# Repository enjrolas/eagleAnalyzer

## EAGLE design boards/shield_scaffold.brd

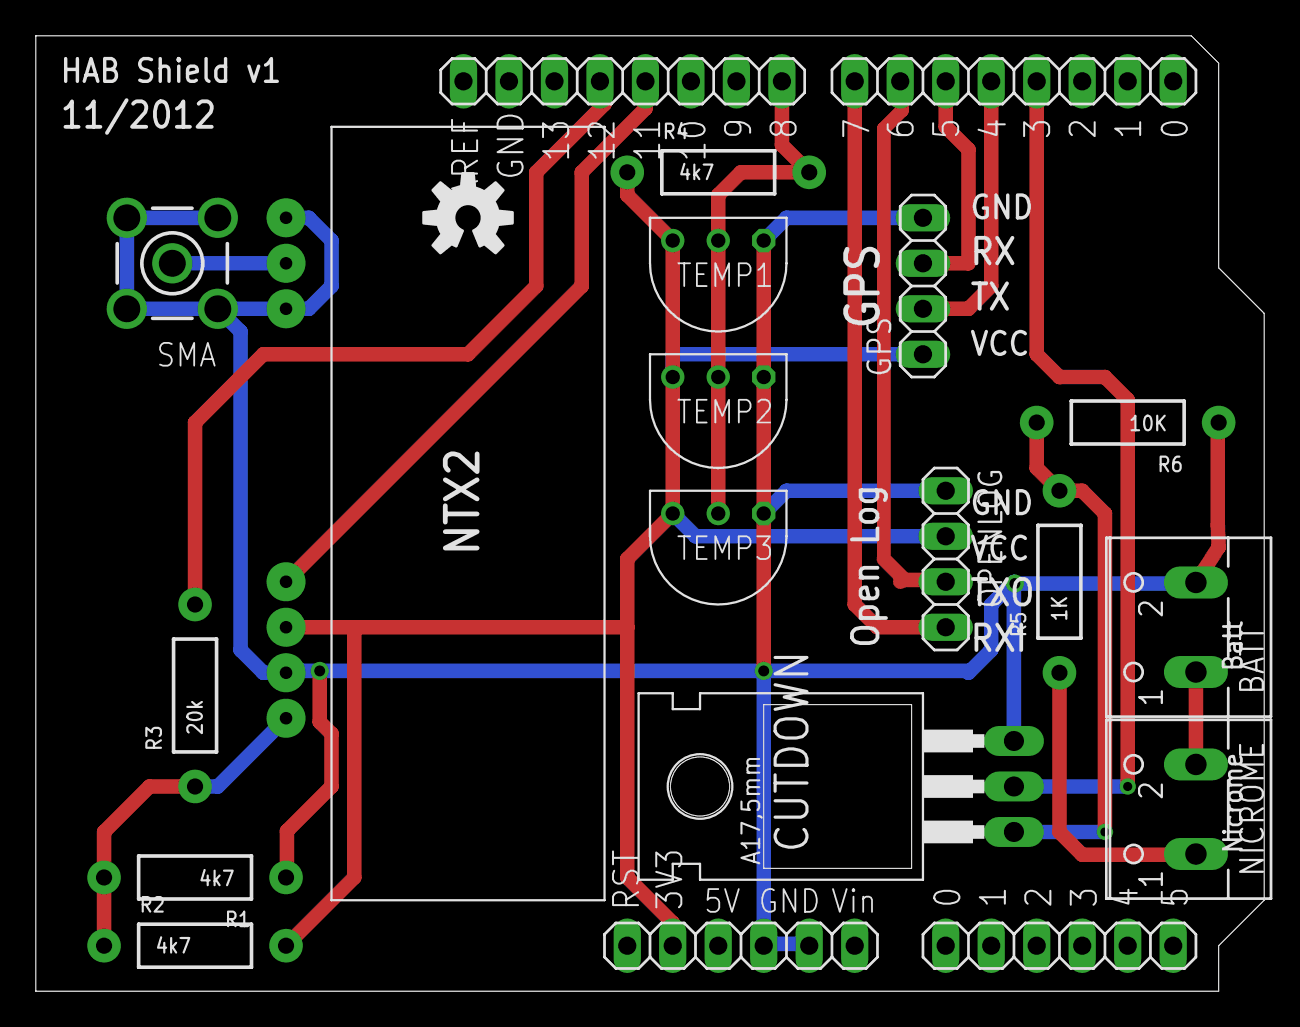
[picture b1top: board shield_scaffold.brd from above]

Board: 2 copper layers, 68.6 x 53.3 mm, 21 parts (0 on the bottom side), 16 nets.

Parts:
BATT: 9V; W237-102
CUTDOWN: BUZ21; TO220
GPS: 1X04
NICROME: Wire; W237-102
OPENLOG: 1X04
R1, R2, R4: 4k7; AXIAL-0.4
R3: 20k; AXIAL-0.4
R5: 1K; AXIAL-0.4
R6: 10K; AXIAL-0.4
SMA: LTI-SASF54GT
TEMP1, TEMP2, TEMP3: DS1821
U$1: POWER; 1X06
U$2: ANALOG; 1X06
U$3: DIGITAL_0_7; 1X08
U$4: DIGITAL_8_13; 1X08
U$5: NTX2
U$6: OSHW-LOGOM; OSHW-LOGO-M

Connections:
9V+: BATT.1, NICROME.2
CUT: CUTDOWN.2, U$3.5
CUTLOAD: NICROME.1, R5.P$1
GND: BATT.2, CUTDOWN.3, GPS.4, OPENLOG.1, R1.P$1, R6.P$1, SMA.3, SMA.4, SMA.5, TEMP1.P$1, TEMP2.P$1, TEMP3.P$1, U$1.4, U$1.5, U$5.0V
GPSRX: GPS.3, U$3.3
GPSTX: GPS.2, U$3.4
LOGI: OPENLOG.4, U$3.1
LOGO: OPENLOG.3, U$3.2
unnamed: CUTDOWN.1, R5.P$2, R6.P$2
NTX2E: U$4.5, U$5.EN
NTX2IO: R3.P$2, U$4.4
RFGND: SMA.2, U$5.RFGND, U$5.RFGND2
RFOUT: SMA.1, U$5.RFOUT
TEMP: R4.P$2, TEMP1.P$2, TEMP2.P$2, TEMP3.P$2, U$4.8
TXD: R1.P$2, R2.P$1, R3.P$1, U$5.TXD
VCC: GPS.1, OPENLOG.2, R2.P$2, R4.P$1, TEMP1.P$3, TEMP2.P$3, TEMP3.P$3, U$1.2, U$5.VCC

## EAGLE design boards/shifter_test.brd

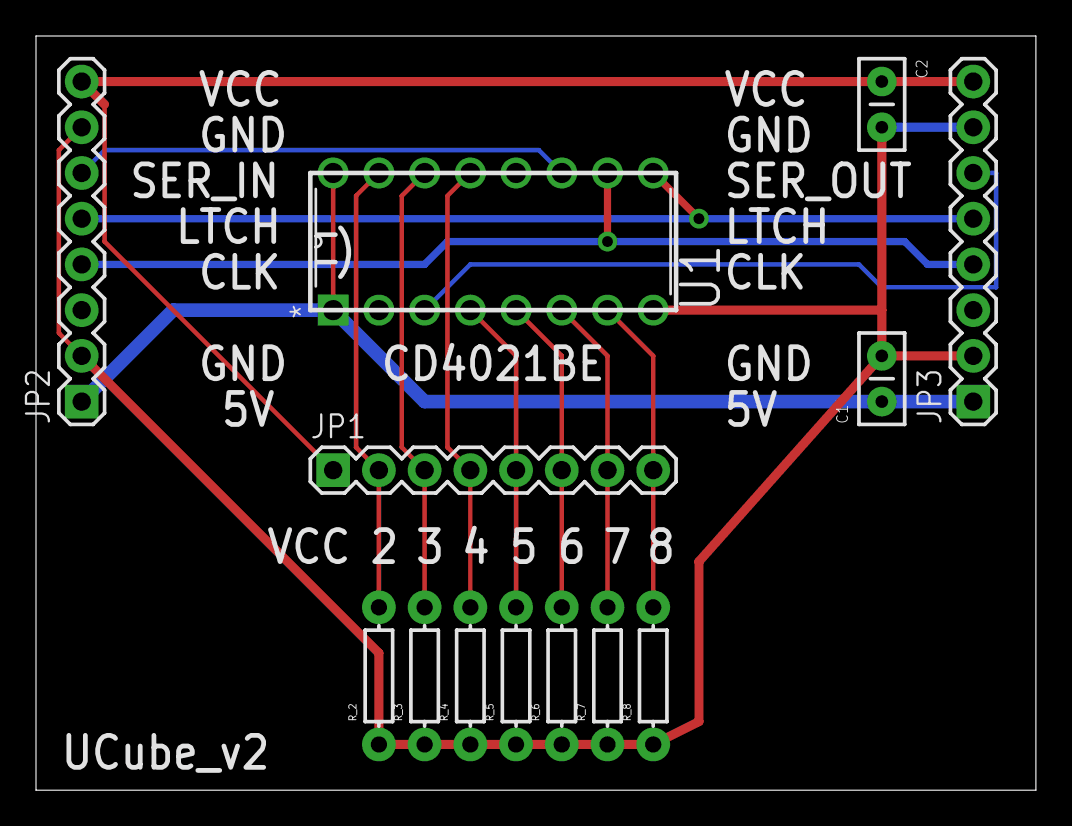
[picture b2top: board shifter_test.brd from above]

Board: 2 copper layers, 55.5 x 41.9 mm, 13 parts (0 on the bottom side), 14 nets.

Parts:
C1, C2: 0.1µf; CAP-PTH-SMALL2
JP1: JP1_LED_HEADER; 1X08
JP2: JP2_SER_IN; 1X08
JP3: JP3_SER_OUT; 1X08
R_2, R_3, R_4, R_5, R_6, R_7, R_8: AXIAL-0.3
U1: CD4021BE; DIP254P762X508-16

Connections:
5V: C1.1, JP2.1, JP3.1, U1.1, U1.16
CLOCK: JP2.4, JP3.4, U1.10
GND: C1.2, C2.2, JP2.2, JP2.7, JP3.2, JP3.7, R_2.P$1, R_3.P$1, R_4.P$1, R_5.P$1, R_6.P$1, R_7.P$1, R_8.P$1, U1.8
LATCH: JP2.5, JP3.5, U1.9
P2: JP1.2, R_2.P$2, U1.15
P3: JP1.3, R_3.P$2, U1.14
P4: JP1.4, R_4.P$2, U1.13
P5: JP1.5, R_5.P$2, U1.4
P6: JP1.6, R_6.P$2, U1.5
P7: JP1.7, R_7.P$2, U1.6
P8: JP1.8, R_8.P$2, U1.7
SERIAL_IN: JP2.6, U1.11
SERIAL_OUT: JP3.6, U1.3
VCC: C2.1, JP1.1, JP2.8, JP3.8

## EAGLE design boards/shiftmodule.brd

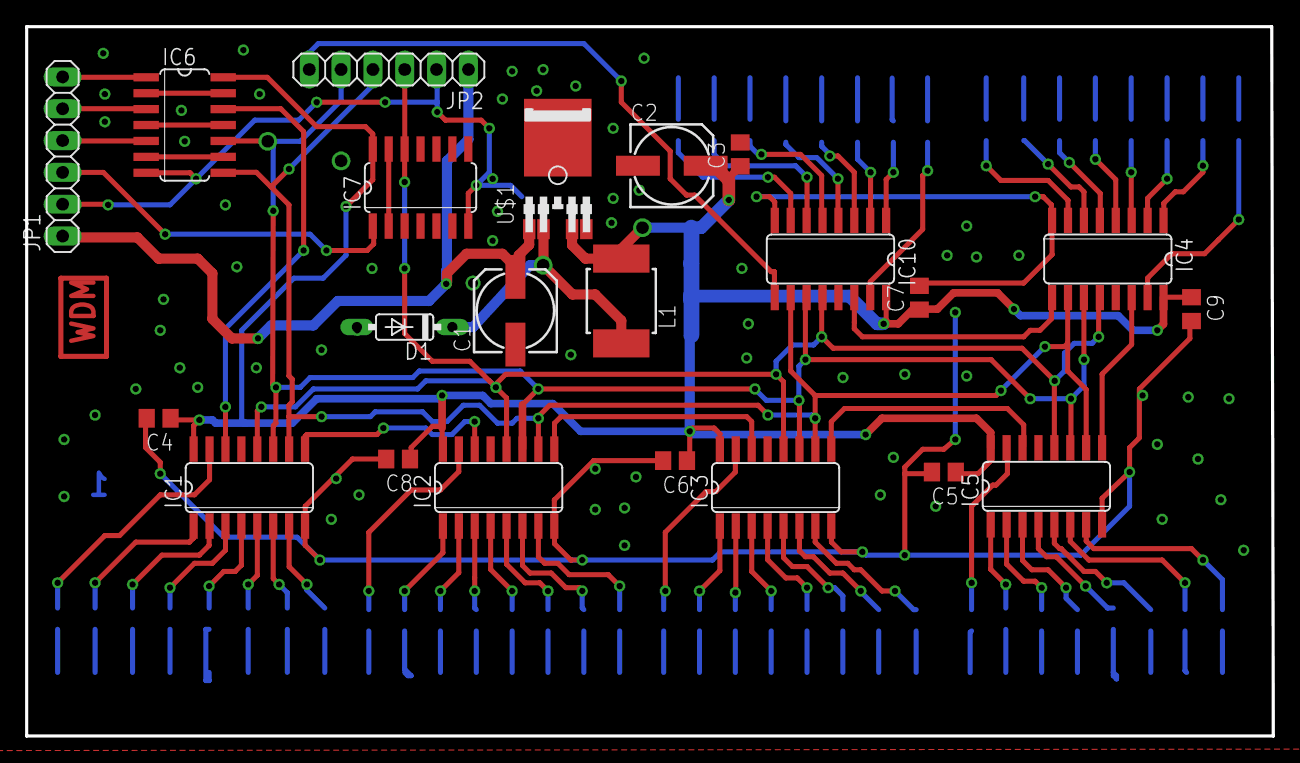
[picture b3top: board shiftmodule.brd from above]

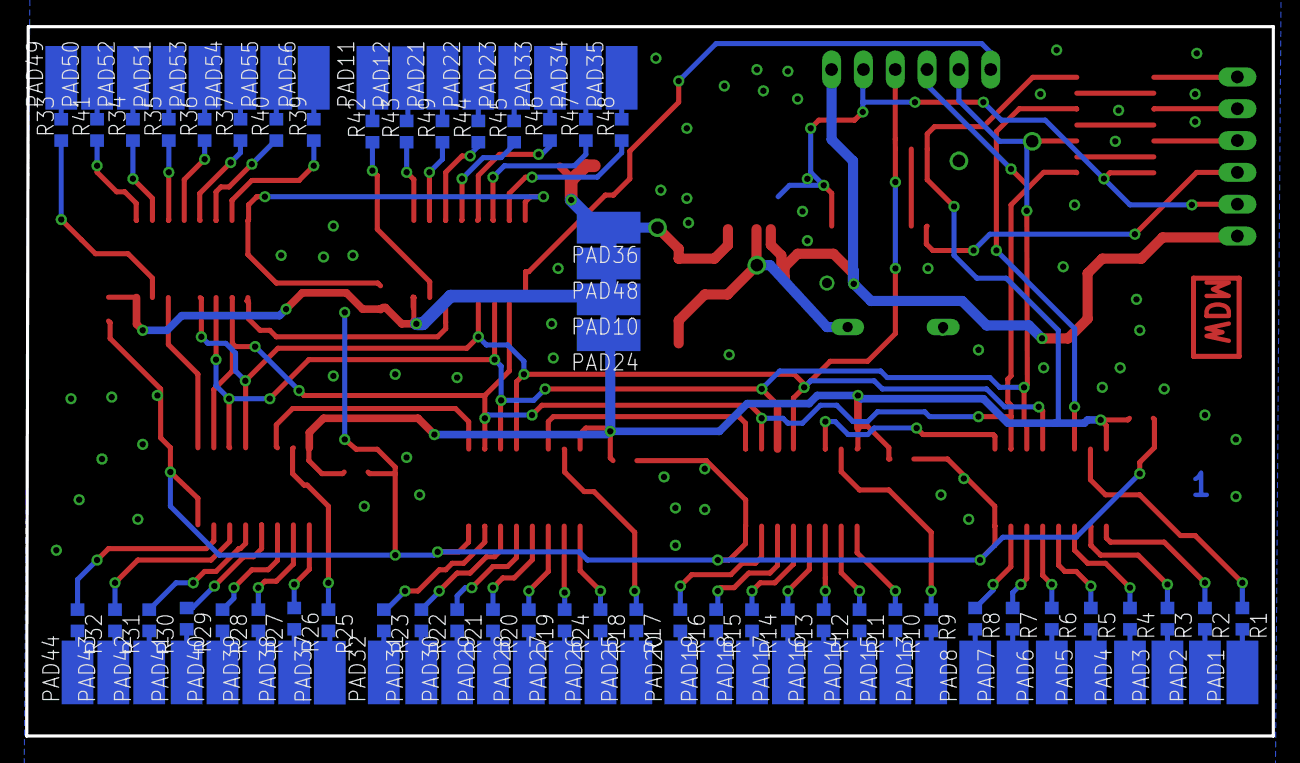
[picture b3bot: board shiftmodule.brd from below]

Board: 2 copper layers, 99.5 x 56.6 mm, 122 parts (100 on the bottom side), 118 nets.

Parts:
C1, C2: 153CLV-0605
C3, C4, C5, C6, C7, C8, C9: C0805
D1: 1N4148DO35-7; DO35-7
IC1, IC2, IC3, IC4, IC5, IC10: 74LS595D; SO16
IC6, IC7: 74HC04D; SO14
JP1, JP2: 1X06
L1: MS85
PAD1, PAD2, PAD3, PAD4, PAD5, PAD6, PAD7, PAD8, PAD10, PAD11, PAD12, PAD13, PAD14, PAD15, PAD16, PAD17, PAD18, PAD19, PAD20, PAD21, PAD22, PAD23, PAD24, PAD25, PAD26, PAD27, PAD28, PAD29, PAD30, PAD31, PAD32, PAD33, PAD34, PAD35, PAD36, PAD37, PAD38, PAD39, PAD40, PAD41, PAD42, PAD43, PAD44, PAD48, PAD49, PAD50, PAD51, PAD52, PAD53, PAD54, PAD55, PAD56: SMD2,54-5,08
R1, R2, R3, R4, R5, R6, R7, R8, R9, R10, R11, R12, R13, R14, R15, R16, R17, R18, R19, R20, R21, R22, R23, R24, R25, R26, R27, R28, R29, R30, R31, R32, R33, R34, R35, R36, R37, R39, R40, R41, R42, R43, R44, R45, R46, R47, R48, R49: R0603
U$1: AP1507; TO252-5-11

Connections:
GND: C1.-, C2.-, C3.2, C4.2, C5.2, C6.2, C7.2, C8.2, C9.2, D1.A, IC1.8, IC2.8, IC3.8, IC4.8, IC5.8, IC6.7, IC7.7, IC10.8, JP1.2, JP2.2, U$1.3, U$1.5
unnamed: IC6.2, IC6.13
unnamed: IC2.9, IC3.14
unnamed: IC3.9, IC5.14
unnamed: IC10.9, JP2.6
unnamed: IC6.4, IC6.11
unnamed: IC6.6, IC6.9
unnamed: IC6.1, JP1.6
unnamed: IC6.3, JP1.5
unnamed: IC6.5, JP1.4
unnamed: IC7.1, JP1.3
unnamed: PAD1.1, R1.2
unnamed: PAD2.1, R2.2
unnamed: PAD3.1, R3.2
unnamed: IC4.14, IC5.9
unnamed: PAD4.1, R4.2
unnamed: PAD5.1, R5.2
unnamed: PAD6.1, R6.2
unnamed: PAD7.1, R7.2
unnamed: PAD8.1, R8.2
unnamed: PAD13.1, R9.2
unnamed: PAD15.1, R10.2
unnamed: PAD14.1, R11.2
unnamed: PAD16.1, R12.2
unnamed: PAD17.1, R13.2
unnamed: PAD18.1, R14.2
unnamed: PAD19.1, R15.2
unnamed: PAD20.1, R16.2
unnamed: PAD25.1, R17.2
unnamed: PAD26.1, R18.2
unnamed: PAD28.1, R19.2
unnamed: PAD29.1, R20.2
unnamed: PAD30.1, R21.2
unnamed: PAD31.1, R22.2
unnamed: PAD32.1, R23.2
unnamed: PAD27.1, R24.2
unnamed: PAD37.1, R25.2
unnamed: PAD38.1, R26.2
unnamed: PAD39.1, R27.2
unnamed: PAD40.1, R28.2
unnamed: PAD41.1, R29.2
unnamed: PAD42.1, R30.2
unnamed: PAD43.1, R31.2
unnamed: PAD44.1, R32.2
unnamed: PAD49.1, R33.2
unnamed: PAD52.1, R34.2
unnamed: PAD51.1, R35.2
unnamed: PAD53.1, R36.2
unnamed: PAD54.1, R37.2
unnamed: PAD56.1, R39.2
unnamed: PAD55.1, R40.2
unnamed: PAD50.1, R41.2
unnamed: IC1.9, IC2.14
unnamed: IC7.2, IC7.13
unnamed: IC4.9, IC10.14
unnamed: PAD11.1, R42.2
unnamed: PAD12.1, R43.2
unnamed: PAD22.1, R44.2
unnamed: PAD23.1, R45.2
unnamed: PAD33.1, R46.2
unnamed: PAD34.1, R47.2
unnamed: PAD35.1, R48.2
unnamed: PAD21.1, R49.2
unnamed: D1.C, L1.1, U$1.2
unnamed: IC4.7, R39.1
unnamed: IC4.5, R37.1
unnamed: IC4.6, R40.1
unnamed: IC4.4, R36.1
unnamed: IC4.3, R35.1
unnamed: IC4.2, R34.1
unnamed: IC4.1, R41.1
unnamed: IC4.15, R33.1
unnamed: IC10.15, R42.1
unnamed: IC10.1, R43.1
unnamed: IC10.2, R49.1
unnamed: IC10.3, R44.1
unnamed: IC10.4, R45.1
unnamed: IC10.5, R46.1
unnamed: IC10.6, R47.1
unnamed: IC10.7, R48.1
unnamed: IC5.7, R32.1
unnamed: IC5.6, R31.1
unnamed: IC5.5, R30.1
unnamed: IC5.4, R29.1
unnamed: IC5.3, R28.1
unnamed: IC5.2, R27.1
unnamed: IC5.1, R26.1
unnamed: IC5.15, R25.1
unnamed: IC3.7, R23.1
unnamed: IC3.6, R22.1
unnamed: IC3.5, R21.1
unnamed: IC3.4, R20.1
unnamed: IC3.3, R19.1
unnamed: IC3.2, R24.1
unnamed: IC3.1, R18.1
unnamed: IC3.15, R17.1
unnamed: IC2.7, R16.1
unnamed: IC2.6, R15.1
unnamed: IC2.5, R14.1
unnamed: IC2.4, R13.1
unnamed: IC2.3, R12.1
unnamed: IC2.2, R11.1
unnamed: IC2.1, R10.1
unnamed: IC2.15, R9.1
unnamed: IC1.15, R1.1
unnamed: IC1.1, R2.1
unnamed: IC1.7, R8.1
unnamed: IC1.6, R7.1
unnamed: IC1.5, R6.1
unnamed: IC1.4, R5.1
unnamed: IC1.3, R4.1
unnamed: IC1.2, R3.1
RCK: IC1.12, IC2.12, IC3.12, IC4.12, IC5.12, IC7.12, IC10.12, JP2.3
SCK: IC1.11, IC2.11, IC3.11, IC4.11, IC5.11, IC6.10, IC10.11, JP2.5
SCL: IC1.10, IC2.10, IC3.10, IC4.10, IC5.10, IC6.8, IC10.10, JP2.4
SER: IC1.14, IC6.12
VCC: C2.+, C3.1, C4.1, C5.1, C6.1, C7.1, C8.1, C9.1, IC1.16, IC2.16, IC3.16, IC4.16, IC5.16, IC6.14, IC7.14, IC10.16, L1.2, PAD10.1, PAD24.1, PAD36.1, PAD48.1, U$1.4
VIN: C1.+, JP1.1, JP2.1, U$1.1

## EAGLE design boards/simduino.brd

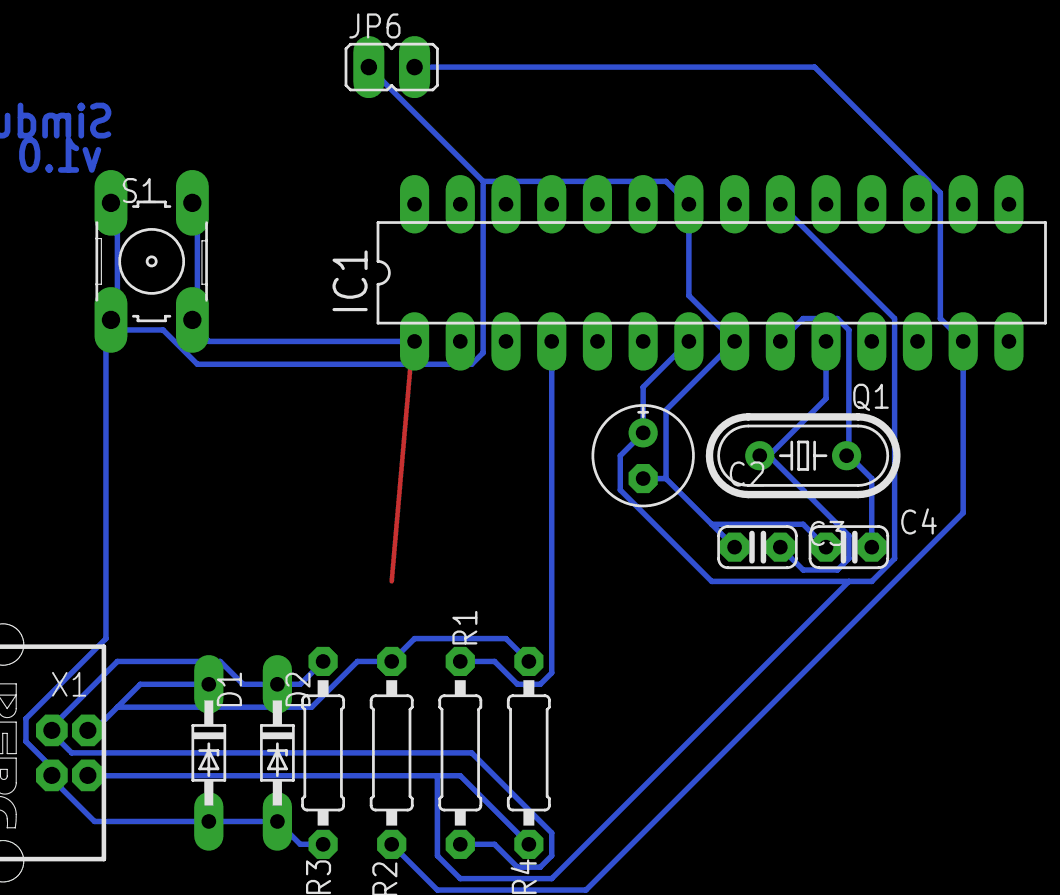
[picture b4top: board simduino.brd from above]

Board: 2 copper layers, 14 parts (0 on the bottom side), 9 nets.

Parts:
C2: 10uF; E2,5-6E
C3, C4: 22p; C025-024X044
D1, D2: 3V6; DO34Z7
IC1: ATMEGA168-20P; DIL28-3
JP6: JP1
Q1: 16MHz; HC49/S
R1, R2: 68; 0207/10
R3: 1M; 0207/10
R4: 1k5; 0207/10
S1: B3F-10XX
X1: PN61729

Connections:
+5USB: C2.+, IC1.7, IC1.20, R4.1, X1.1
D+: D2.C, R1.1, R3.2, X1.3
D-: D1.C, R2.1, R4.2, X1.2
GND: C2.-, C3.1, C4.1, D1.A, D2.A, IC1.8, IC1.22, JP6.1, R3.1, S1.1, S1.2, X1.4
unnamed: IC1.13, JP6.2, R2.2
unnamed: IC1.1, S1.3, S1.4
unnamed: IC1.4, R1.2
unnamed: C3.2, IC1.10, Q1.1
unnamed: C4.2, IC1.9, Q1.2

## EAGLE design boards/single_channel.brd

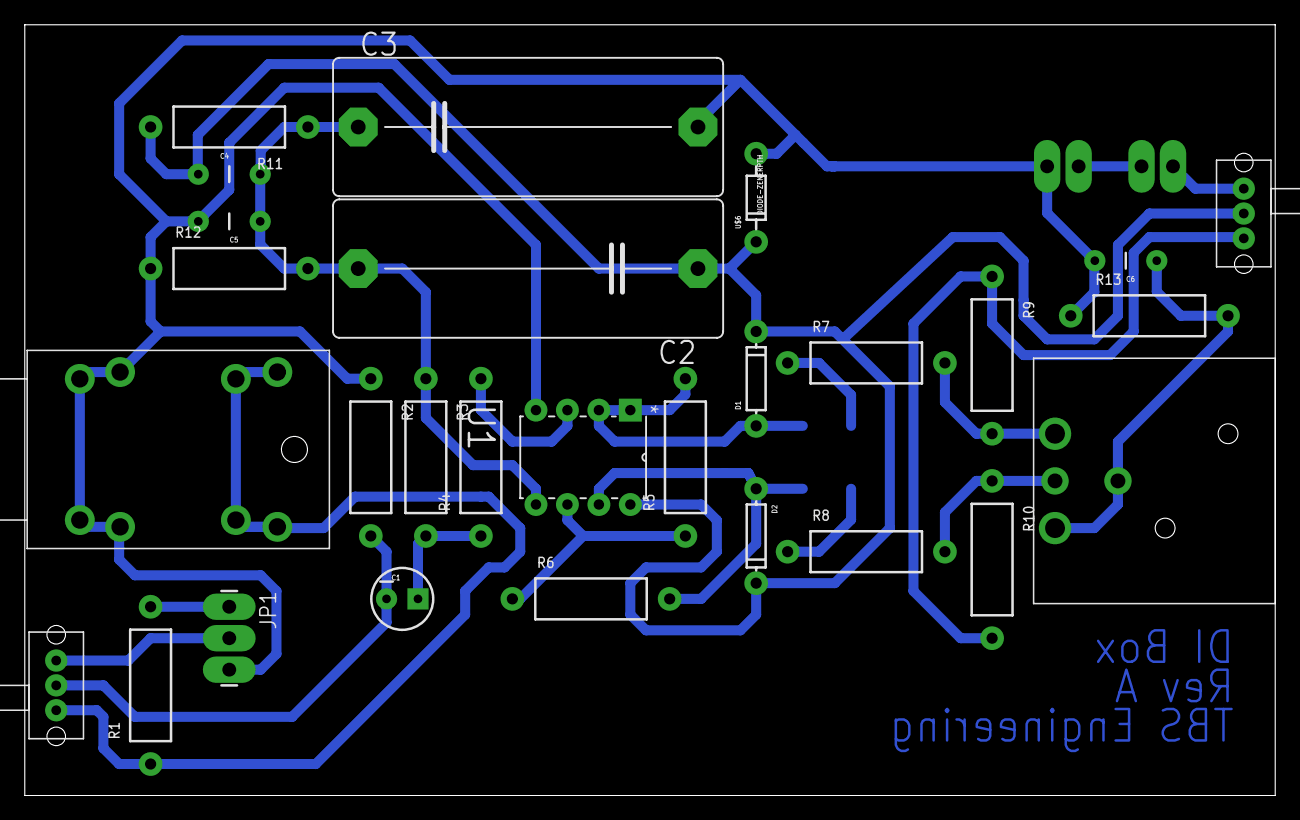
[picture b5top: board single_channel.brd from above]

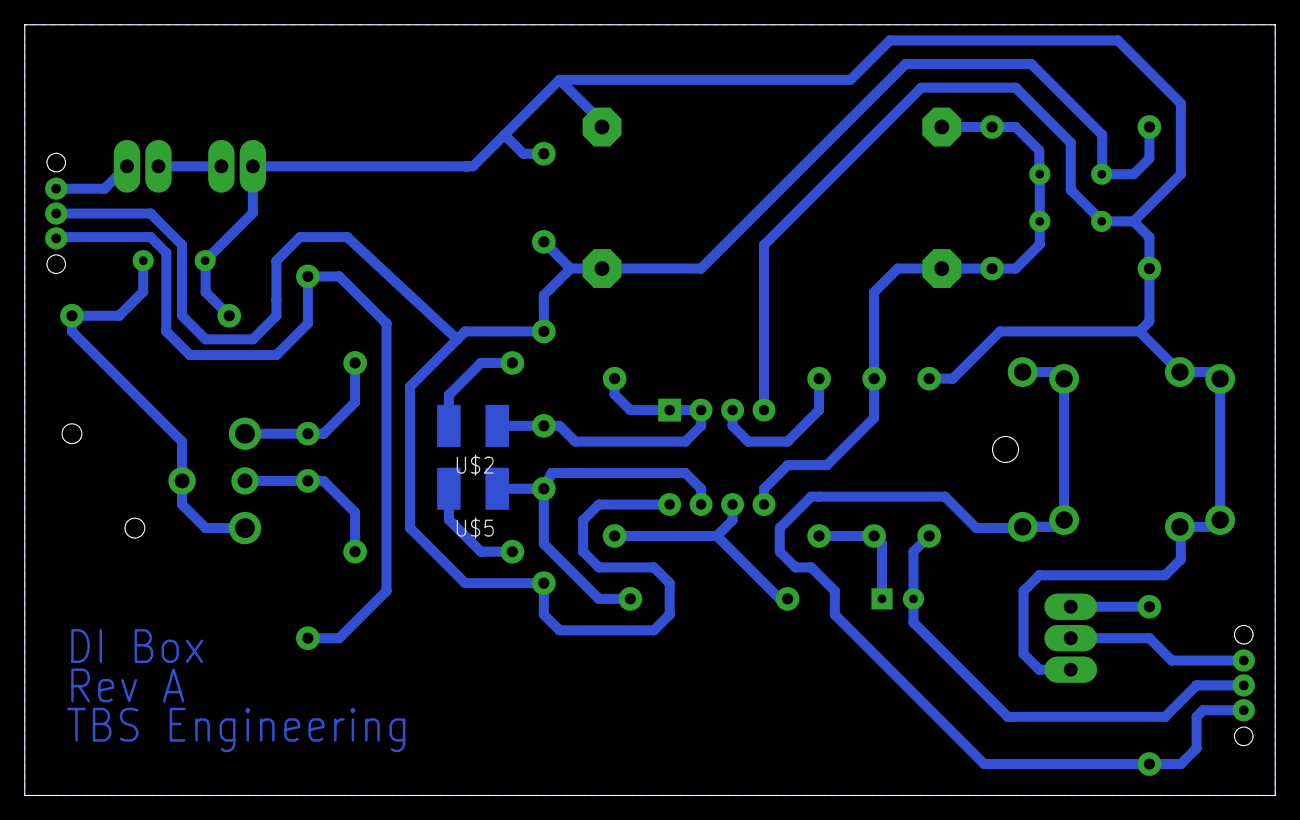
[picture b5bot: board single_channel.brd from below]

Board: 2 copper layers, 101.0 x 62.2 mm, 33 parts (2 on the bottom side), 20 nets.

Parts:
C1: CPOL-RADIAL-10UF-25V
C2, C3: C27.5B11
C4, C5, C6: CAP-PTH-5MM
D1, D2: DIODE-1N4148
DRILEGEND: DRILEGEND
J1: ACJMMHD; MHD
JP1: 1X03_LONGPADS
JP2, JP3: 1X02_LONGPADS
R1, R2, R3, R4, R5, R6, R7, R8, R9, R10, R11, R12, R13: AXIAL-0.5
U1: TL072CP; DIP254P762X508-8
U$1: AC3M; AC3MAH
U$2, U$5: CAP; C1812
U$3, U$4: SPDT; SPDT-SLIDE
U$6: DIODE-ZENERPTH; DIODE-ZENER

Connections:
GND: C3.2, C5.2, C6.2, J1.1, J1.4, J1.7, J1.10, JP1.3, JP3.2, R2.P$1, R12.P$1, R13.P$1, U1.4, U$6.P$2
unnamed: JP1.1, R1.P$2
unnamed: J1.3, J1.6, J1.9, J1.12, R1.P$1, U$3.3
unnamed: JP1.2, U$3.1
unnamed: C1.2, R2.P$2, U$3.2
unnamed: C1.1, R3.P$2, R4.P$1
unnamed: D1.A, R5.P$2, U1.1, U1.2, U$2.1
unnamed: R4.P$2, U1.3
unnamed: R5.P$1, R6.P$1, U1.6
unnamed: C2.2, C3.1, C4.2, C5.1, R3.P$1, R11.P$1, R12.P$2, U1.5
unnamed: C2.1, C4.1, D1.C, D2.C, R11.P$2, U1.8, U$4.2, U$6.P$1
unnamed: D2.A, R6.P$2, U1.7, U$5.1
unnamed: R8.P$2, R10.P$1, U$1.3
unnamed: R9.P$1, R10.P$2, U$4.1
unnamed: R7.P$2, R9.P$2, U$1.2
unnamed: R7.P$1, U$2.2
unnamed: R8.P$1, U$5.2
unnamed: JP2.2, JP3.1
unnamed: JP2.1, U$4.3
unnamed: C6.1, R13.P$2, U$1.1, U$1.G

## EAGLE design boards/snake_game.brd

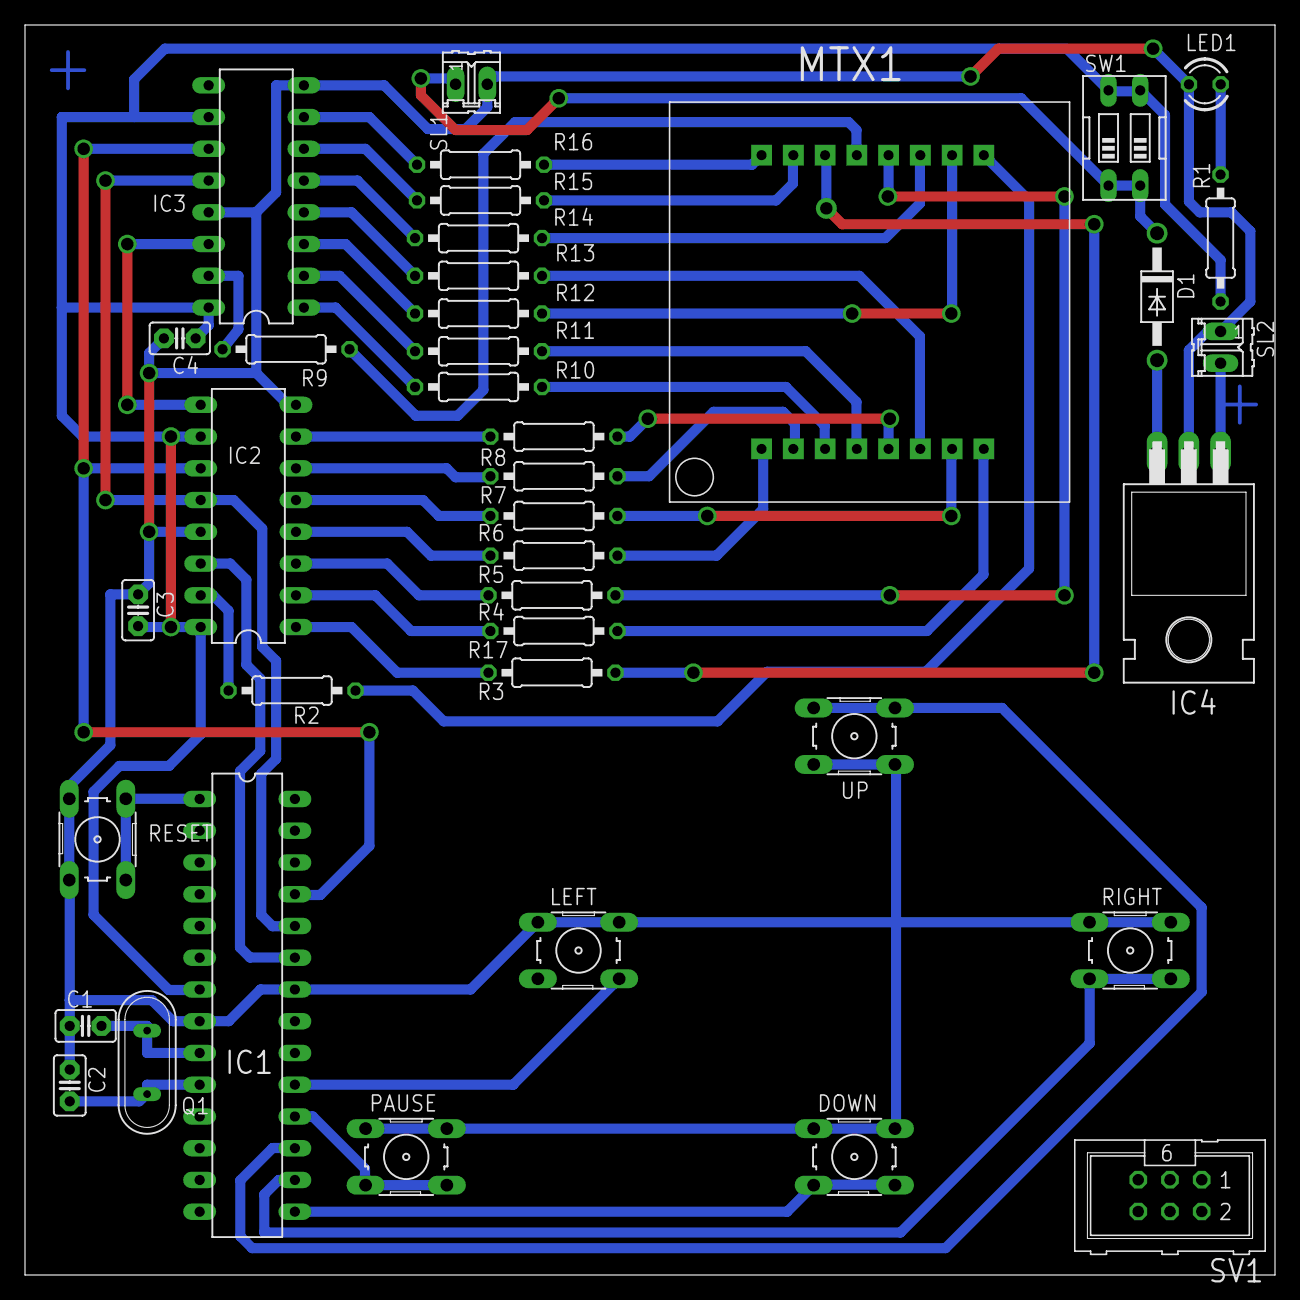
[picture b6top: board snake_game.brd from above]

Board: 2 copper layers, 100.0 x 100.0 mm, 39 parts (0 on the bottom side), 50 nets.

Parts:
C1, C2, C3, C4: 22pF; C2.5-2
D1: 1N4001; DO41-10
DOWN: DOWN; B3F-10XX
IC1: MEGA8-P; DIL28-3
IC2, IC3: 74HC595N; DIL16
IC4: 7805T; TO220H
LED1: Verde; LED3MM
LEFT: LEFT; B3F-10XX
MTX1: LED_DOT_MATRIX_8X8_CPM12088B; MATRIX_8X8_CPM12088B
PAUSE: PAUSE; B3F-10XX
Q1: 16MHz; QS
R1: 330R; 0207/10
R2, R3, R4, R5, R6, R7, R8, R9, R10, R11, R12, R13, R14, R15, R16, R17: 220R; 0207/10
RESET: RESET; B3F-10XX
RIGHT: RIGHT; B3F-10XX
SL1: Alimentacao 5V; 02P
SL2: Alimentacao Regulada; 02P
SV1: ISP; ML6
SW1: EDG-02
UP: UP; B3F-10XX

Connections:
GND: C1.1, C2.1, C3.1, C4.2, DOWN.1, DOWN.2, IC1.8, IC1.22, IC2.8, IC2.13, IC3.8, IC3.13, IC4.2, LED1.K, LEFT.1, LEFT.2, PAUSE.1, PAUSE.2, RESET.3, RESET.4, RIGHT.1, RIGHT.2, SL1.2, SL2.1, SV1.6, UP.1, UP.2
unnamed: MTX1.9, R2.2
unnamed: IC1.1, RESET.1, RESET.2, SV1.5
unnamed: C2.2, IC1.10, Q1.1
unnamed: C1.2, IC1.9, Q1.2
unnamed: IC1.19, LEFT.3, LEFT.4, SV1.3
unnamed: DOWN.3, DOWN.4, IC1.15
unnamed: IC1.16, RIGHT.3, RIGHT.4
unnamed: IC1.17, SV1.4, UP.3, UP.4
unnamed: IC4.1, SL2.2
unnamed: IC1.18, PAUSE.3, PAUSE.4, SV1.1
unnamed: D1.A, IC4.3
unnamed: IC1.23, IC2.14
unnamed: IC1.24, IC2.12, IC3.12
unnamed: IC1.25, IC2.11, IC3.11
unnamed: D1.C, SL1.1, SW1.1, SW1.2
unnamed: LED1.A, R1.2
unnamed: IC2.9, IC3.14
unnamed: MTX1.14, R3.2
unnamed: MTX1.8, R17.2
unnamed: MTX1.12, R4.2
unnamed: MTX1.1, R5.2
unnamed: MTX1.7, R6.2
unnamed: MTX1.2, R7.2
unnamed: IC2.7, R8.1
unnamed: MTX1.13, R9.2
unnamed: MTX1.3, R10.2
unnamed: MTX1.4, R11.2
unnamed: MTX1.10, R12.2
unnamed: MTX1.6, R13.2
unnamed: MTX1.11, R14.2
unnamed: MTX1.15, R15.2
unnamed: MTX1.16, R16.2
unnamed: IC3.7, R16.1
unnamed: IC2.15, R2.1
unnamed: IC3.6, R15.1
unnamed: IC3.5, R14.1
unnamed: IC3.4, R13.1
unnamed: IC3.3, R12.1
unnamed: IC3.2, R11.1
unnamed: IC3.1, R10.1
unnamed: IC3.15, R9.1
unnamed: IC2.1, R3.1
unnamed: IC2.3, R4.1
unnamed: IC2.4, R5.1
unnamed: IC2.5, R6.1
unnamed: IC2.6, R7.1
unnamed: MTX1.5, R8.2
unnamed: IC2.2, R17.1
VCC: C3.2, C4.1, IC1.7, IC2.10, IC2.16, IC3.10, IC3.16, R1.1, SV1.2, SW1.3, SW1.4

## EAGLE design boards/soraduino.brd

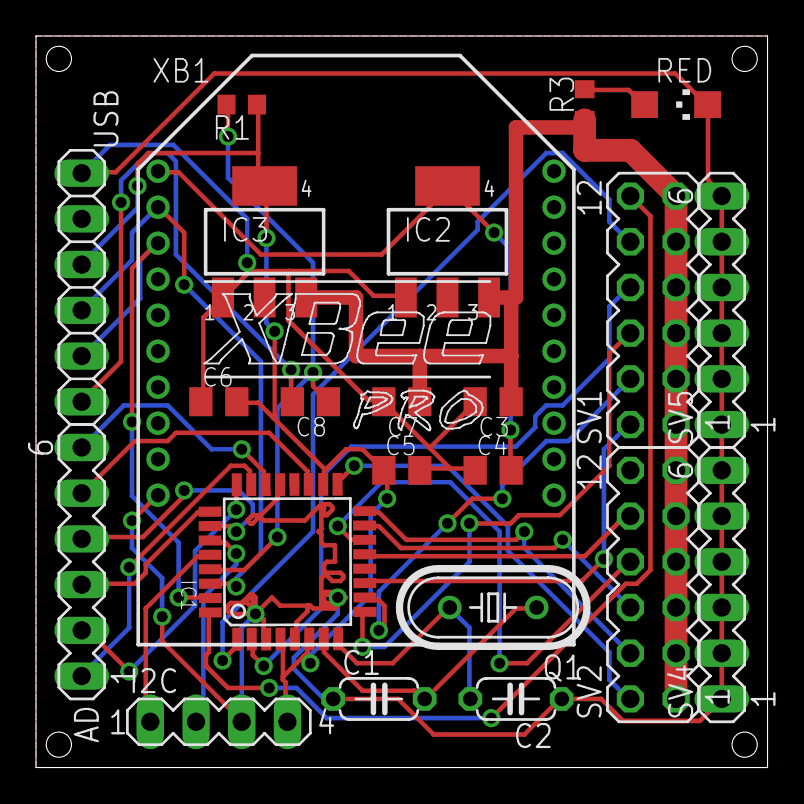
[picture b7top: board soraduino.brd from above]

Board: 2 copper layers, 40.6 x 40.6 mm, 23 parts (0 on the bottom side), 30 nets.

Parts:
AD: AD; MA06-1
C1, C2: 22p; C050-024X044
C3, C5, C7, C8: 0.1u; C0805K
C4, C6: 47u; C0805K
I2C: I2C; MA04-1
IC1: ATMEGA168-AU; TQFP32-08
IC2, IC3: 317EMP; SOT223
Q1: QT; HC49/S
R1, R3: 1k; R0603
RED: CHIPLED_1206
SV1: Servo0; MA06-2
SV2: Servo1; MA06-2
SV4, SV5: GND; MA06-1
USB: 1X06
XB1: XBEE-PRO

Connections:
GND: C1.1, C2.1, C3.2, C4.1, C5.2, C6.1, C7.2, I2C.3, IC1.3, IC1.5, IC1.21, IC2.1, IC3.1, RED.C, SV4.1, SV4.2, SV4.3, SV4.4, SV4.5, SV4.6, SV5.1, SV5.2, SV5.3, SV5.4, SV5.5, SV5.6, USB.6, XB1.10
unnamed: C8.2, USB.1
unnamed: C8.1, IC1.29, R1.2
unnamed: IC1.30, USB.3, XB1.2
unnamed: C1.2, IC1.7, Q1.1
unnamed: C2.2, IC1.8, Q1.2
unnamed: C4.2, IC2.4, XB1.1
unnamed: C5.1, C6.2, I2C.4, IC1.4, IC1.6, IC1.18, IC3.4, R1.1, USB.4
unnamed: IC1.32, SV1.12
unnamed: IC1.1, SV1.10
unnamed: R3.2, RED.A
unnamed: IC1.2, SV1.8
unnamed: IC1.9, SV1.6
unnamed: IC1.10, SV1.4
unnamed: IC1.11, SV1.2
unnamed: IC1.13, SV2.10
unnamed: IC1.14, SV2.8
unnamed: IC1.15, SV2.6
unnamed: IC1.16, SV2.4
unnamed: IC1.17, SV2.2
unnamed: AD.6, IC1.22
unnamed: AD.5, IC1.19
unnamed: AD.4, IC1.26
unnamed: AD.3, IC1.25
unnamed: AD.2, IC1.24
unnamed: AD.1, IC1.23
unnamed: I2C.1, IC1.28
unnamed: I2C.2, IC1.27
unnamed: IC1.31, USB.2, XB1.3
VCC: C3.1, C7.1, IC2.3, IC3.3, R3.1, SV1.1, SV1.3, SV1.5, SV1.7, SV1.9, SV1.11, SV2.1, SV2.3, SV2.5, SV2.7, SV2.9, SV2.11

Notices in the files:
parts and their libraries:
SparkFun-Resistors: Licensing: CC v3.0 Share-Alike You are welcome to use this library for commercial purposes.
